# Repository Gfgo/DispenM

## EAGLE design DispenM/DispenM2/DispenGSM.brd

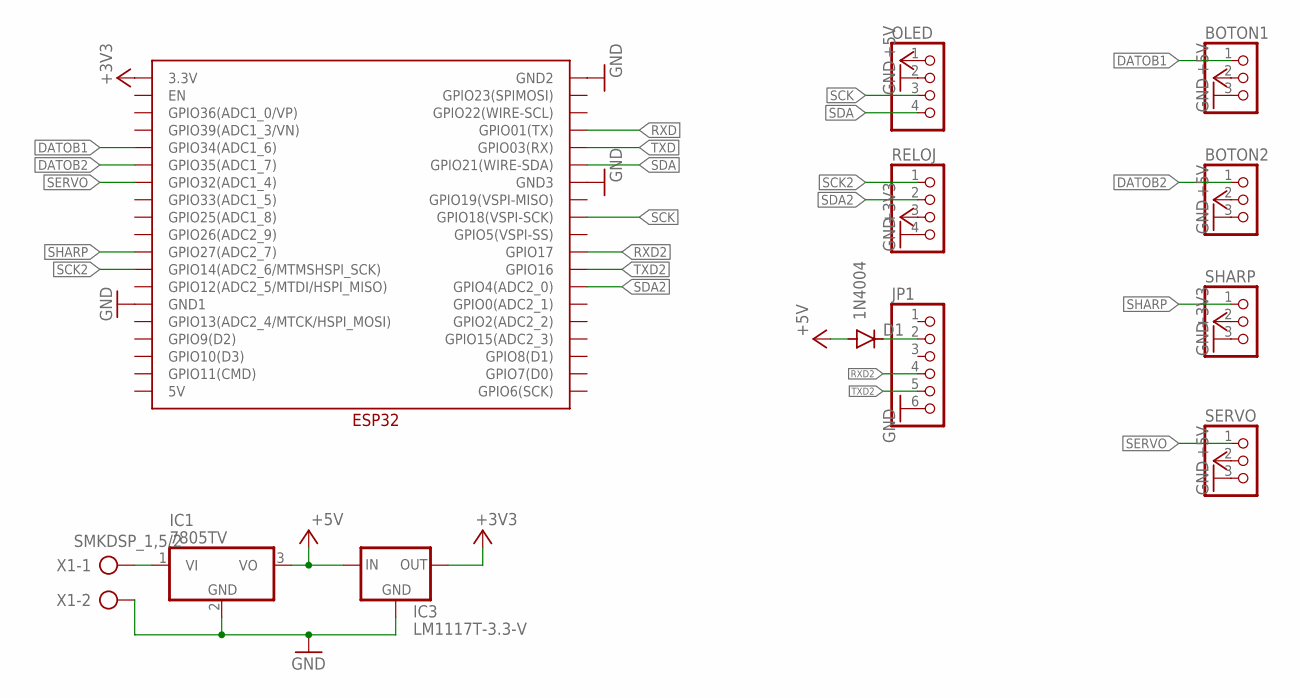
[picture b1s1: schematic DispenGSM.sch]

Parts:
BOTON1, BOTON2: PINHD-1X3; 1X03
D1: 1N4004; DO41-10
IC1: 7805TV; TO220V
IC3: LM1117T-3.3-V; TO220V
JP1: PINHD-1X6; 1X06
OLED: PINHD-1X4; 1X04
RELOJ: PINHD-1X4; 1X04
SERVO: PINHD-1X3; 1X03
SHARP: PINHD-1X3; 1X03
U$1: ESP32WESP32W; ESP32W
X1: SMKDSP_1,5/2

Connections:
+3V3: IC3.2 (OUT), RELOJ.3, SHARP.2, U$1.3.3V
+5V: BOTON1.2, BOTON2.2, D1.A, IC1.3 (VO), IC3.3 (IN), OLED.1, SERVO.2
DATOB1: BOTON1.1, U$1.GPIO34 (GPIO34(ADC1_6))
DATOB2: BOTON2.1, U$1.GPIO35 (GPIO35(ADC1_7))
GND: BOTON1.3, BOTON2.3, IC1.2 (GND), IC3.1 (GND), JP1.6, OLED.2, RELOJ.4, SERVO.3, SHARP.3, U$1.GND1, U$1.GND2, U$1.GND3, X1.2
unnamed: IC1.1 (VI), X1.1
unnamed: D1.C, JP1.2
RXD: U$1.TX (GPIO01(TX))
RXD2: JP1.4, U$1.GPIO17
SCK: OLED.3, U$1.GPIO18 (GPIO18(VSPI-SCK))
SCK2: RELOJ.1, U$1.GPIO14 (GPIO14(ADC2_6/MTMSHSPI_SCK))
SDA: OLED.4, U$1.GPIO21 (GPIO21(WIRE-SDA))
SDA2: RELOJ.2, U$1.GPIO4 (GPIO4(ADC2_0))
SERVO: SERVO.1, U$1.GPIO32 (GPIO32(ADC1_4))
SHARP: SHARP.1, U$1.GPIO27 (GPIO27(ADC2_7))
TXD: U$1.RX (GPIO03(RX))
TXD2: JP1.5, U$1.GPIO16

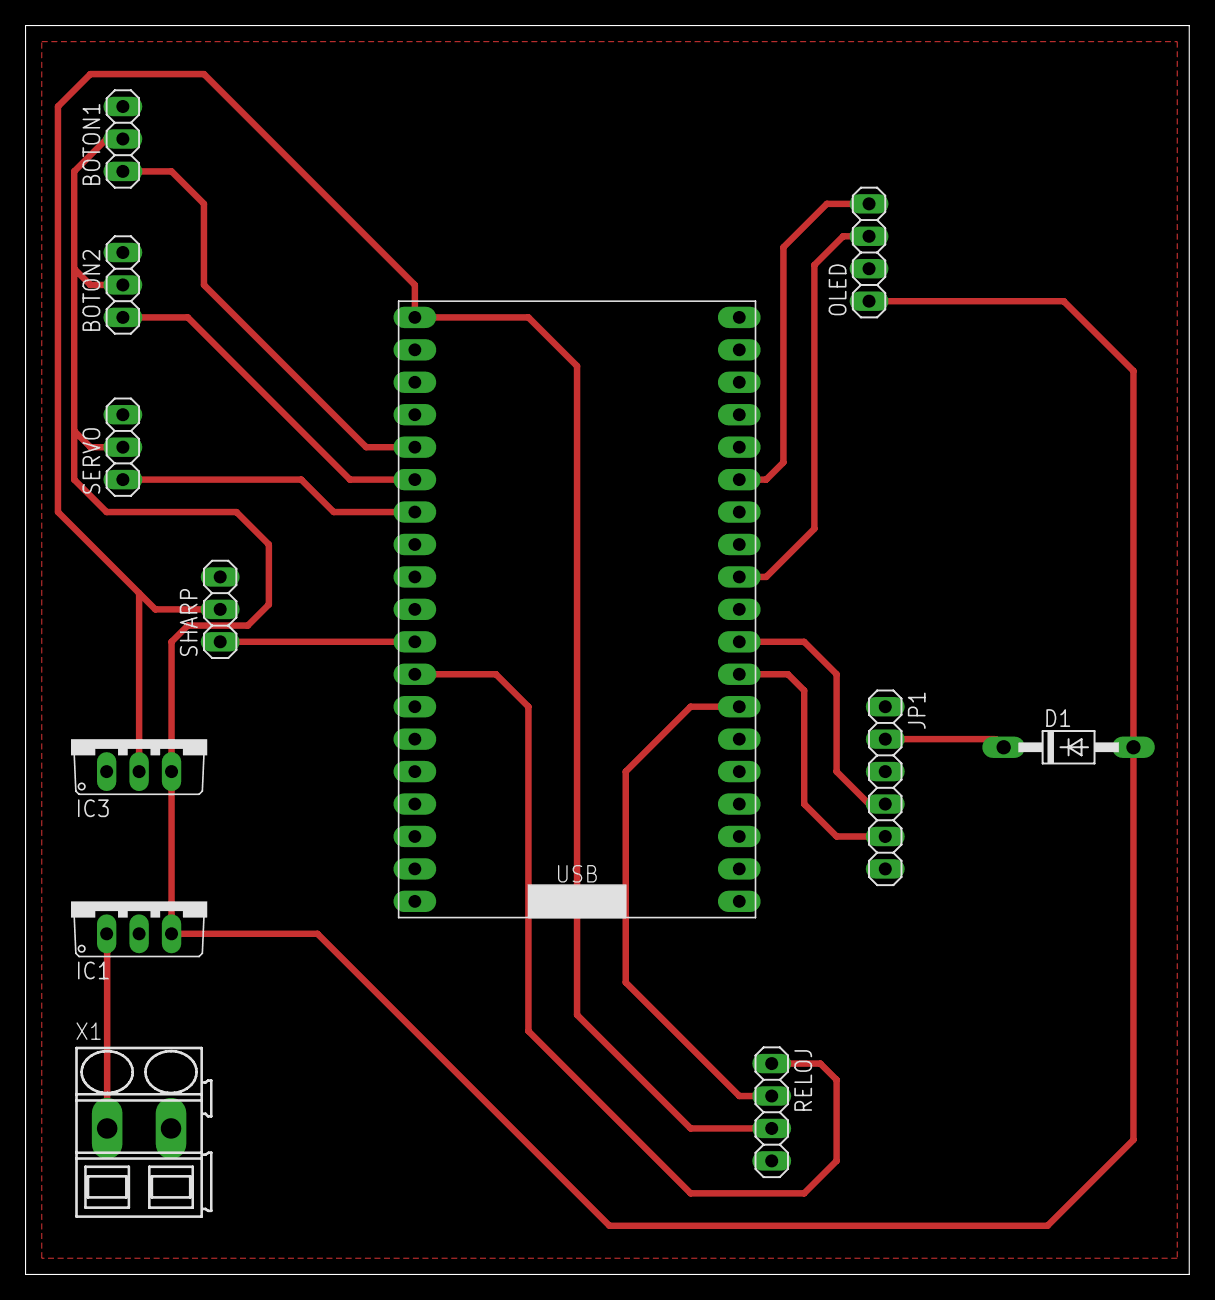
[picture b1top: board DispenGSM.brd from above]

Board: 2 copper layers, 91.1 x 97.8 mm, 12 parts (0 on the bottom side), 15 nets.

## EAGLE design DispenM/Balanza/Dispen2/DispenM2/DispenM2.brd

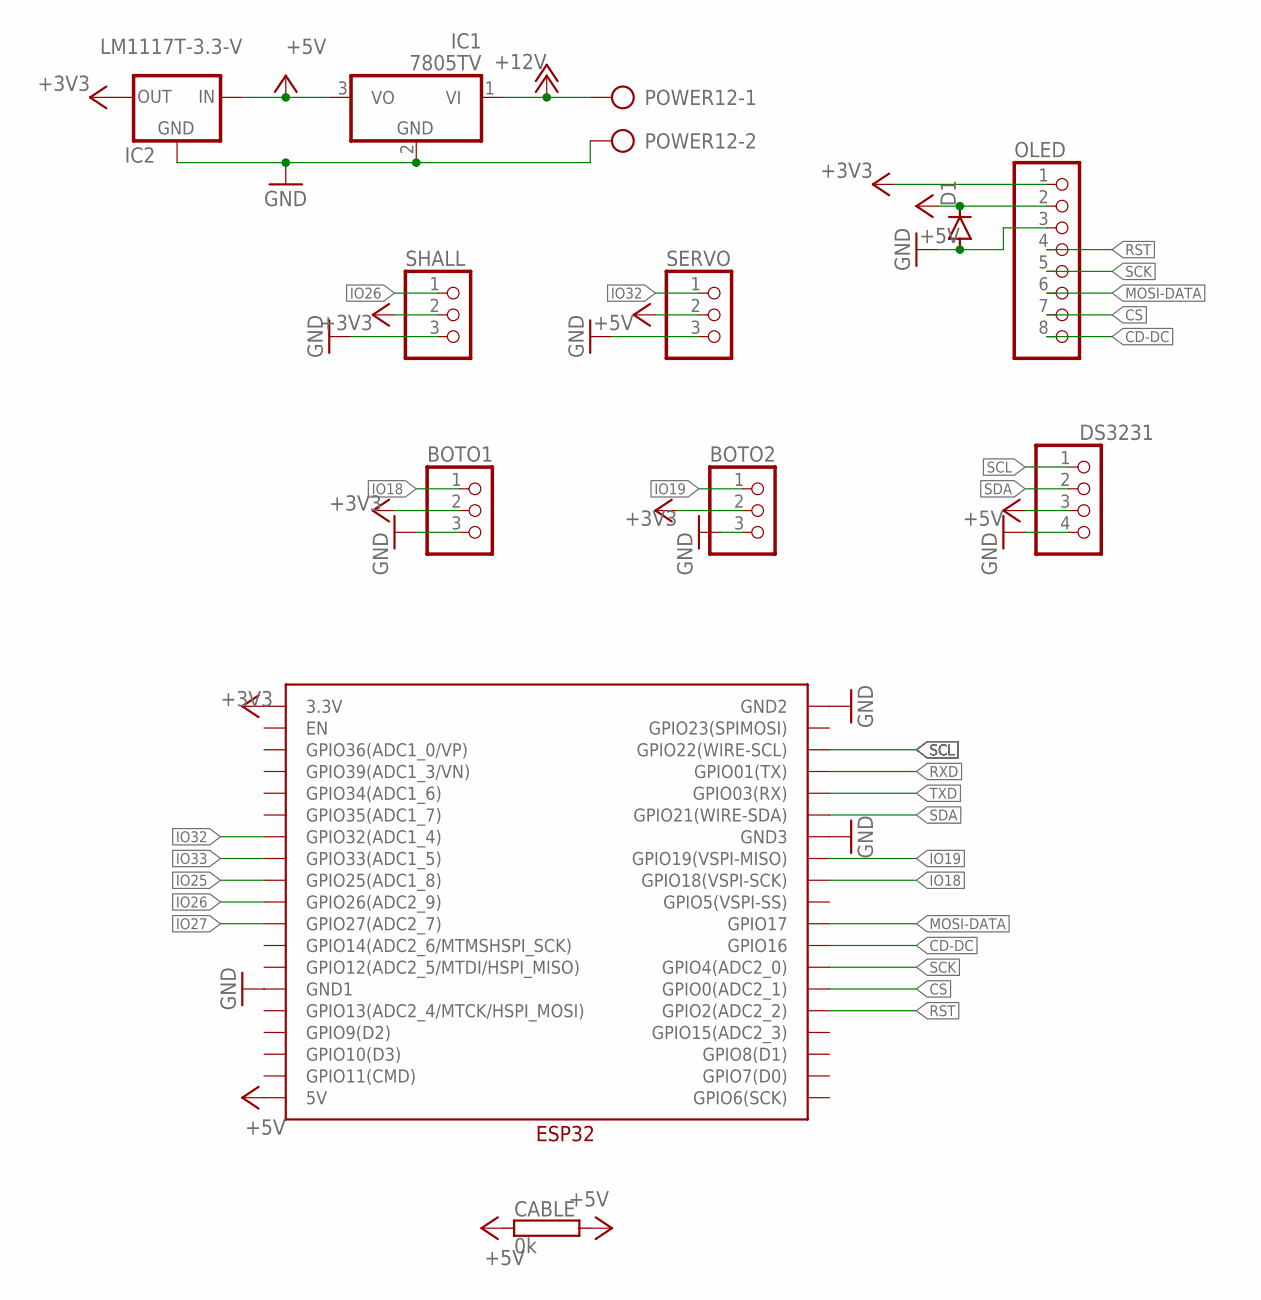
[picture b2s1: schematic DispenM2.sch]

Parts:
BOTO1, BOTO2: PINHD-1X3; 1X03
CABLE: 0k; CA4100
D1: DIODE-SOD81; SOD81
DS3231: PINHD-1X4; 1X04
IC1: 7805TV; TO220V
IC2: LM1117T-3.3-V; TO220V
OLED: PINHD-1X8; 1X08
POWER12: AK500/2
SERVO: PINHD-1X3; 1X03
SHALL: PINHD-1X3; 1X03
U$1: ESP32WESP32W; ESP32W

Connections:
+3V3: BOTO1.2, BOTO2.2, IC2.2 (OUT), OLED.1, SHALL.2, U$1.3.3V
+5V: CABLE.1, CABLE.2, D1.C, DS3231.3, IC1.3 (VO), IC2.3 (IN), OLED.2, SERVO.2, U$1.5V
+12V: IC1.1 (VI), POWER12.1
CD-DC: OLED.8, U$1.GPIO16
CS: OLED.7, U$1.GPIO0 (GPIO0(ADC2_1))
GND: BOTO1.3, BOTO2.3, D1.A, DS3231.4, IC1.2 (GND), IC2.1 (GND), OLED.3, POWER12.2, SERVO.3, SHALL.3, U$1.GND1, U$1.GND2, U$1.GND3
IO18: BOTO1.1, U$1.GPIO18 (GPIO18(VSPI-SCK))
IO19: BOTO2.1, U$1.GPIO19 (GPIO19(VSPI-MISO))
IO25: U$1.GPIO25 (GPIO25(ADC1_8))
IO26: SHALL.1, U$1.GPIO26 (GPIO26(ADC2_9))
IO27: U$1.GPIO27 (GPIO27(ADC2_7))
IO32: SERVO.1, U$1.GPIO32 (GPIO32(ADC1_4))
IO33: U$1.GPIO33 (GPIO33(ADC1_5))
MOSI-DATA: OLED.6, U$1.GPIO17
RST: OLED.4, U$1.GPIO2 (GPIO2(ADC2_2))
RXD: U$1.TX (GPIO01(TX))
SCK: OLED.5, U$1.GPIO4 (GPIO4(ADC2_0))
SCL: DS3231.1, U$1.GPIO22 (GPIO22(WIRE-SCL))
SDA: DS3231.2, U$1.GPIO21 (GPIO21(WIRE-SDA))
TXD: U$1.RX (GPIO03(RX))

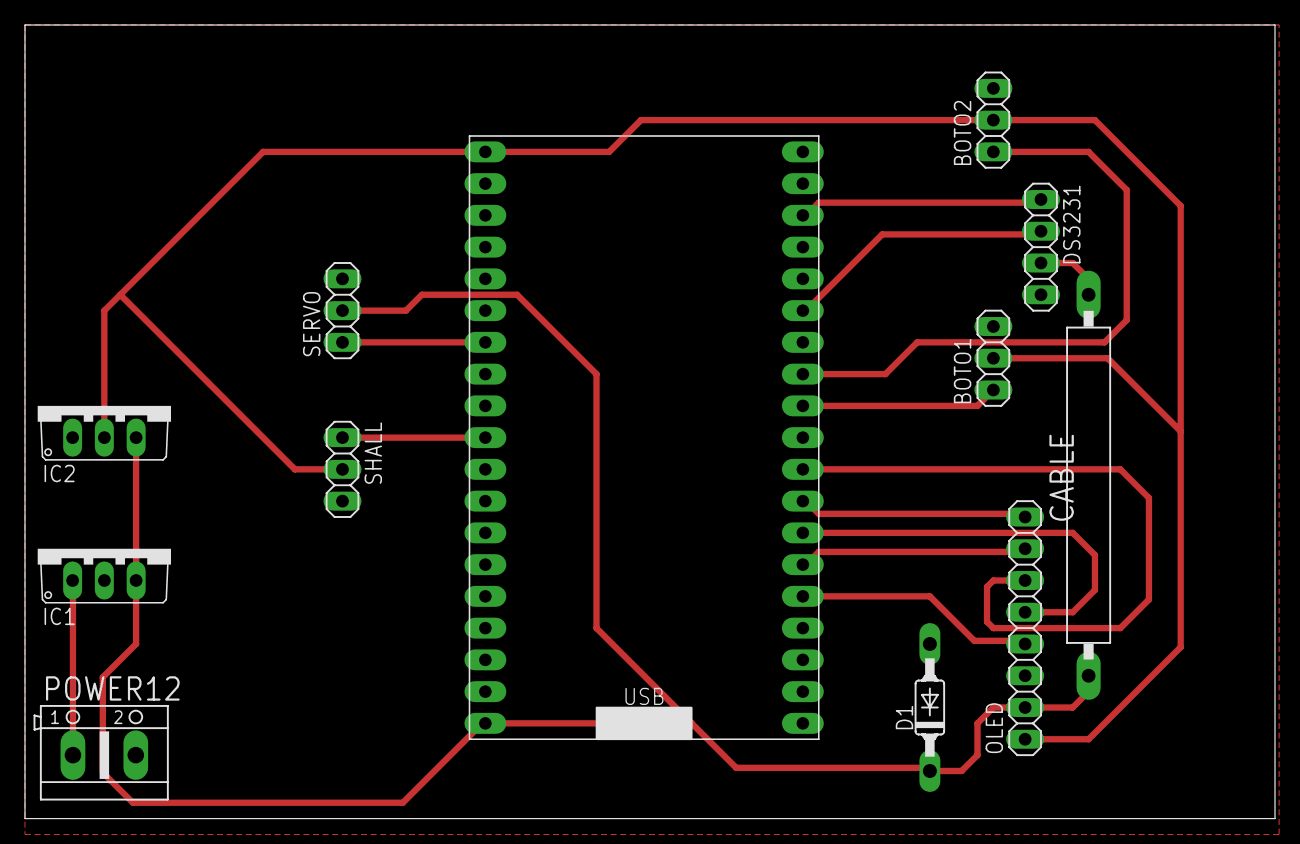
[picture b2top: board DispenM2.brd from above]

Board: 2 copper layers, 100.0 x 63.5 mm, 12 parts (0 on the bottom side), 15 nets.

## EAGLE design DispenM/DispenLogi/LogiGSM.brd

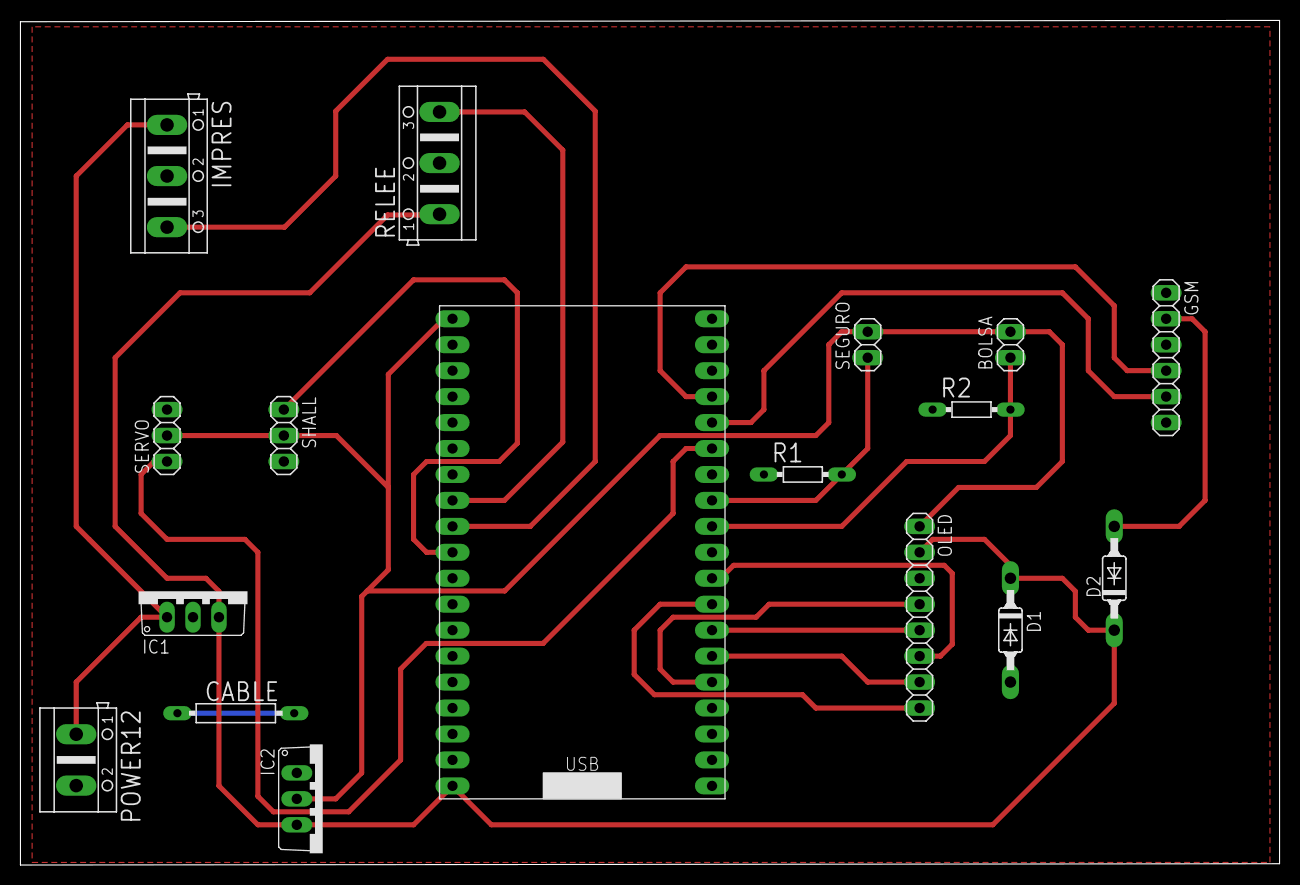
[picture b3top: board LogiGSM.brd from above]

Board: 2 copper layers, 123.2 x 82.7 mm, 17 parts (0 on the bottom side), 18 nets.

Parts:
BOLSA: 1X02
CABLE: 0k; RS1/2
D1, D2: SOD81
GSM: 1X06
IC1: 7805TV; TO220V
IC2: LM1117T-3.3-V; TO220V
IMPRES: AK500/3
OLED: 1X08
POWER12: AK500/2
R1, R2: 1k; RS1/8
RELEE: AK500/3
SEGURO: 1X02
SERVO: 1X03
SHALL: 1X03
U$1: ESP32WESP32W; ESP32W

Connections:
+3V3: BOLSA.2, IC2.2, OLED.1, SEGURO.2, SERVO.2, SHALL.2, U$1.3.3V
+5V: D1.C, D2.C, IC1.3, IC2.3, OLED.2, RELEE.1, U$1.5V
+12V: IC1.1, IMPRES.1, POWER12.1
CD-DC: OLED.8, U$1.GPIO16
CS: OLED.7, U$1.GPIO0
GND: CABLE.1, CABLE.2, D1.A, GSM.6, IC1.2, IC2.1, IMPRES.2, OLED.3, POWER12.2, R1.1, R2.1, RELEE.2, SERVO.3, SHALL.3, U$1.GND1, U$1.GND2, U$1.GND3
IO18: BOLSA.1, R2.2, U$1.GPIO18
IO19: R1.2, SEGURO.1, U$1.GPIO19
IO21: SERVO.1, U$1.GPIO21
IO25: IMPRES.3, U$1.GPIO25
IO26: SHALL.1, U$1.GPIO26
IO33: RELEE.3, U$1.GPIO33
MOSI-DATA: OLED.6, U$1.GPIO17
unnamed: D2.A, GSM.2
RST: OLED.4, U$1.GPIO2
RXD: GSM.4, U$1.TX
SCK: OLED.5, U$1.GPIO4
TXD: GSM.5, U$1.RX

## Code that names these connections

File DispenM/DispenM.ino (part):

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//#error Bluetooth is not enabled! Please run `make menuconfig` to and enable it
//#endif
//
//#define LED_PIN   32 //GPIO32
//#define LED_COUNT 8
//
//Adafruit_RGBLCDShield lcd = Adafruit_RGBLCDShield();
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

//int cont=0;
byte hall=18;                  //GPIO18 sensor hall
byte h=0;
byte h1[]={10,30,50};
//byte h2[4]={5,9,13,17};
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

//int cont=0;
byte hall=18;                  //GPIO18 sensor hall
byte h=0;
byte h1[]={10,30,50};
//byte h2[4]={5,9,13,17};
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U8G2_SSD1306_128X64_NONAME_F_SW_I2C u8g2(U8G2_R0, /* clock=*/ 16, /* data=*/ 17, /* reset=*/ U8X8_PIN_NONE); 
//U8G2_SSD1306_128X64_NONAME_F_4W_HW_SPI u8g2(U8G2_R0, /* cs=*/ 16, /* dc=*/ 17, /* reset=*/ U8X8_PIN_NONE);

int hall=27;                  //GPIO27 sensor hall
byte bot1=34;                  //GPIO34 Boton blanco
byte bot2=35;                  //GPIO35 Boton amarillo

byte h=0;
byte h1[]={10,30,50};          //Horarios apertura puerta
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  Serial.begin(9600);
  u8g2.begin();
  u8g2.enableUTF8Print();
  mervo.attach(32);           //GPIO32 servo
  pinMode (hall, INPUT);      // Sensor hall
  pinMode (bot1, INPUT);      // Sensor bot1
  pinMode (bot2, INPUT);      // Sensor bot2
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
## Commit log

2021-11-12 Inicio ble y motores
2021-11-16 Inclusion de lcd no funca
2021-11-19 Actualización programa
2021-11-22 Arreglos de codigo
2021-11-23 Inclusion de balanza no sirven luces
2021-11-24 Led funciona con errores
2021-11-25 LCD y luces funcionando faltan motores
2021-11-30 Se mejora velocidad quitando lectura de promedio
2021-12-02 Update a esp32
2021-12-07 Todo ok BLE por arduino.
2022-08-02 Update DispenM.ino
    Programación con bluetooth incluido.
2022-11-08 Circuito
2023-06-20 Nuevo programa
2023-07-14 Actualización
2023-07-19 Correccion de plano
2023-07-24 Actualizacion software y pcb
2023-07-25 Correccion pcb
2023-07-26 PCB actualizada
2023-09-12 Cambio de fuente
2023-10-09 Ok sensor Hu
2023-11-08 nuevo circuito
    nuevo circuito
2024-05-22 actualización 22/05
2024-07-05 pantalla y reloj interfaz ok2024
    pantalla y reloj interfaz ok2024
2024-07-09 actualizacion 90/07/2024
    botones servo y hall ok
2024-11-27 27/11/2024
    Actualizacion circuito
